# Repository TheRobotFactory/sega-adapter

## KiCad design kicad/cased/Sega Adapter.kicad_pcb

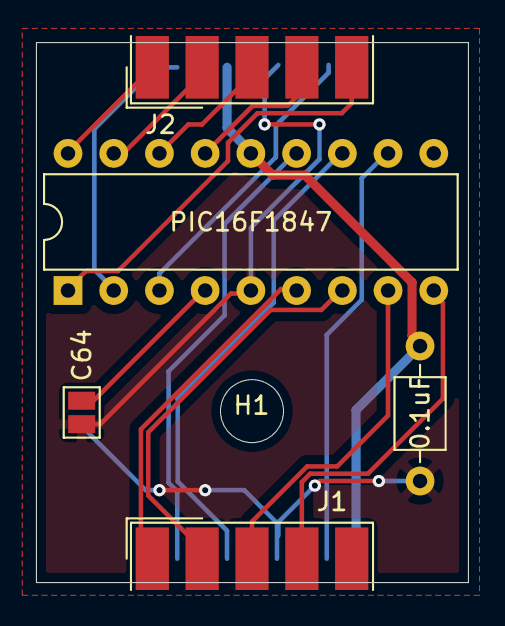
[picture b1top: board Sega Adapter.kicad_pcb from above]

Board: 2 copper layers, 24.0 x 30.0 mm, 6 parts (0 on the bottom side), 17 nets.

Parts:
C1: 0.1uF; C_Axial_L3.8mm_D2.6mm_P7.50mm_Horizontal
H1: MountingHole; MountingHole_3.5mm
J1: Sega; DSUB-9_Male_EdgeMount_P2.77mm
J2: Atari; DSUB-9_Female_EdgeMount_P2.77mm
JP1: C64; SolderJumper-2_P1.3mm_Open_Pad1.0x1.5mm
U1: PIC16F1847; DIP-18_W7.62mm

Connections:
+5V: C1.2, J1.5, J2.7, U1.14
GND: C1.1, J1.8, J2.8, JP1.2, U1.5
unnamed: J1.1, U1.6
unnamed: J1.2, U1.7
unnamed: J1.3, U1.8
unnamed: J1.4, U1.9
unnamed: J1.6, U1.13
unnamed: J1.7, U1.12
unnamed: J1.9, U1.11
unnamed: J2.1, U1.18
unnamed: J2.2, U1.17
unnamed: J2.3, U1.16
unnamed: J2.4, U1.15
unnamed: J2.5, U1.1
unnamed: J2.6, U1.2
unnamed: J2.9, U1.3
unnamed: JP1.1, U1.4

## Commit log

2021-09-10 Add a version to put in a case
    case will be coming later

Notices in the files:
kicad/cased/Sega Adapter.kicad_pcb:
© 2021 Eyvind Bernhardsen
